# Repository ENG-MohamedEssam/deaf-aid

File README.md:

# deaf-aid

## Abstract

#### This project was initially made to help deaf people and normal people to communicate with each other using a small device based on Raspberry pi
#### The projects idea was split into two, the first one is understanding the voice of the normal human being and translate it as text for the deaf person.
#### the second was taking the deaf person's hand gestures and translate it into voice or even text for the normal human being to understand.
#### The first part of the project was does successfully but the second part wasn't completed as the project changed at that time into another project
#### but mainly for the second part we had three ideas one using mediapipe library to make it easy and the second was using deep learning to make it more effective and accurate, both neeeded a camera to take the gestures and a speaker to speak or even take the text on the same LCD.
#### The third idea was to take the hand gestures of the deaf person by making him wear a glove that had flexable resistors, this way we could take the inputs as variable values of the resistors and that would have made it much cheaper.

#### however i'll talk about the first part as it was the one that was finished .
## **Main Components**

#### RaspberryPi , 16x2 Character LCD, Microphone, Power source, Internet source.

#### The following image will give you a glimpse  of the hardware connections

#### The raspberry pi was used as the main processor, the microphone took the voice of the normal human being, then the raspberry pi would process the voice data and recognize it then display it on the LCD 
#### The following two codes were the main codes that were used for the project
#### [input-audio](https://github.com/ENG-MohamedEssam/deaf-aid/blob/main/Speech_Recognition_Test.py)
#### [output-text](https://github.com/ENG-MohamedEssam/deaf-aid/blob/main/LCD_PYTHON.py)
#### also the codes went throught a lot of modification, such as the following code was some kind of LCD driver but to make it easier i used an already made driver in the final code
#### [old-lcd-driver](https://github.com/ENG-MohamedEssam/deaf-aid/blob/main/LCD_PYTHON_OLD.py)
#### So to make the Raspberry pi run the codes on the startup i used the following script to make it launch it while starting up
#### [script](https://github.com/ENG-MohamedEssam/deaf-aid/blob/main/launcher.sh)
#### you will find a video explanation in the following link for the whole project
#### for the power source at first i was using the phone's charger but for the final product i planned to use lipo battery or a power bank 
#### for the internet source i used the phone's usb using usb tethering method but for the final product i planned to use usb dongle or offline voice recognition library 
#### [Explanation](https://drive.google.com/drive/u/0/folders/1KUh7kfPaU8bGa7THwe2R01-4G6Q_rnNO)

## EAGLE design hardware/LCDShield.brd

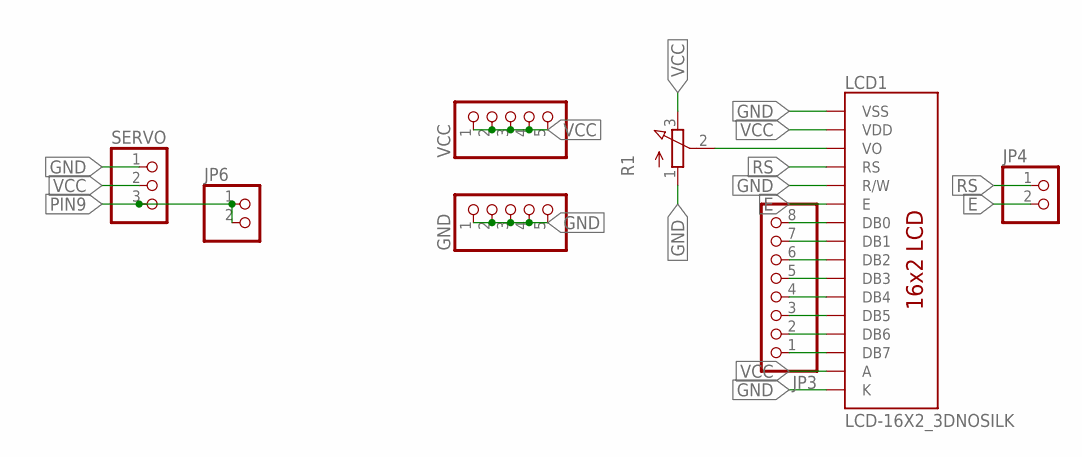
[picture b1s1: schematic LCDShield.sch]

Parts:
GND: PINHD-1X5; 1X05
JP3: PINHD-1X8; 1X08
JP4, JP6: PINHD-1X2; 1X02
LCD1: LCD-16X2_3DNOSILK; LCD-16X2_NOSILK
R1: 3RP/1610N
SERVO: PINHD-1X3; 1X03
VCC: PINHD-1X5; 1X05

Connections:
E: JP4.2, LCD1.6 (E)
GND: GND.1, GND.2, GND.3, GND.4, GND.5, LCD1.1 (VSS), LCD1.5 (R/W), LCD1.16 (K), R1.1 (A), SERVO.1
unnamed: JP3.8, LCD1.7 (DB0)
unnamed: JP3.7, LCD1.8 (DB1)
unnamed: JP3.6, LCD1.9 (DB2)
unnamed: JP3.5, LCD1.10 (DB3)
unnamed: JP3.4, LCD1.11 (DB4)
unnamed: JP3.3, LCD1.12 (DB5)
unnamed: JP3.2, LCD1.13 (DB6)
unnamed: JP3.1, LCD1.14 (DB7)
unnamed: LCD1.3 (VO), R1.2 (S)
PIN9: JP6.1, JP6.2, SERVO.3
RS: JP4.1, LCD1.4 (RS)
VCC: LCD1.2 (VDD), LCD1.15 (A), R1.3 (E), SERVO.2, VCC.1, VCC.2, VCC.3, VCC.4, VCC.5

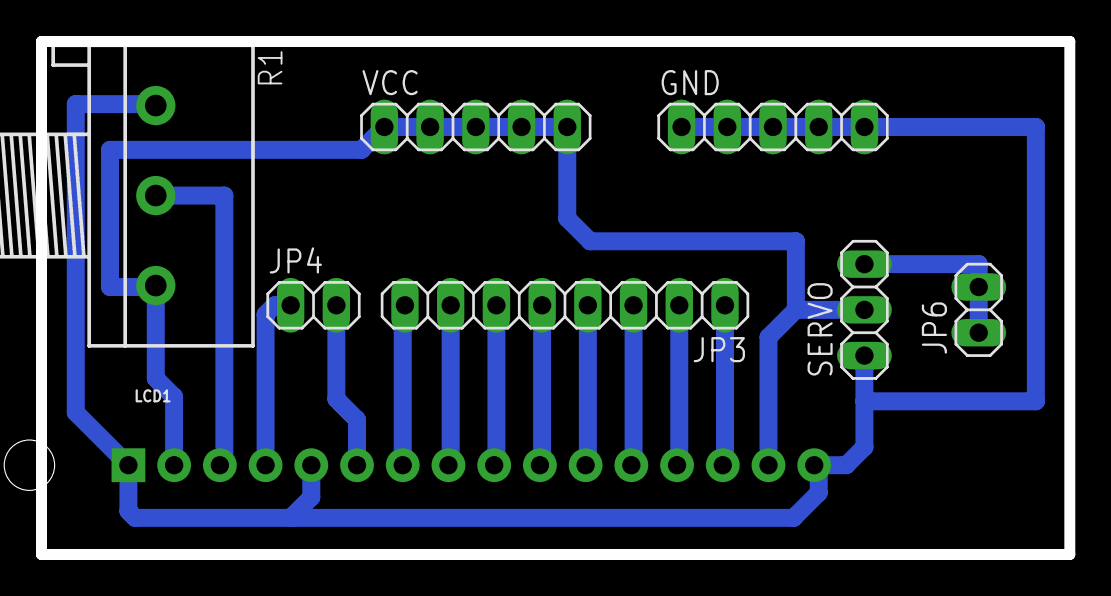
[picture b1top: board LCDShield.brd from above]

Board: 2 copper layers, 57.1 x 28.5 mm, 8 parts (0 on the bottom side), 14 nets.

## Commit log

2022-12-06 edit in readme
2022-12-06 Edit in readme links
